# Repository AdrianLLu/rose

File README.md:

# Rose a MIT OpenAg Personal Food Computer (PFC) community-member-created project
Project URL: https://github.com/AdrianLLu/rose <br>
By Adrian L. Lu <br>
TODO Rose helps you ... <br>
MIT OpenAg Personal Food Computer (PFC) community-member-generated files <br>
For my build diary see: http://adrianllu.com/category/food-computer/ <br>
TODO: You are free to copy, modify, and distribute Rose with attribution under the terms of the <license>. See the LICENSE file for details.

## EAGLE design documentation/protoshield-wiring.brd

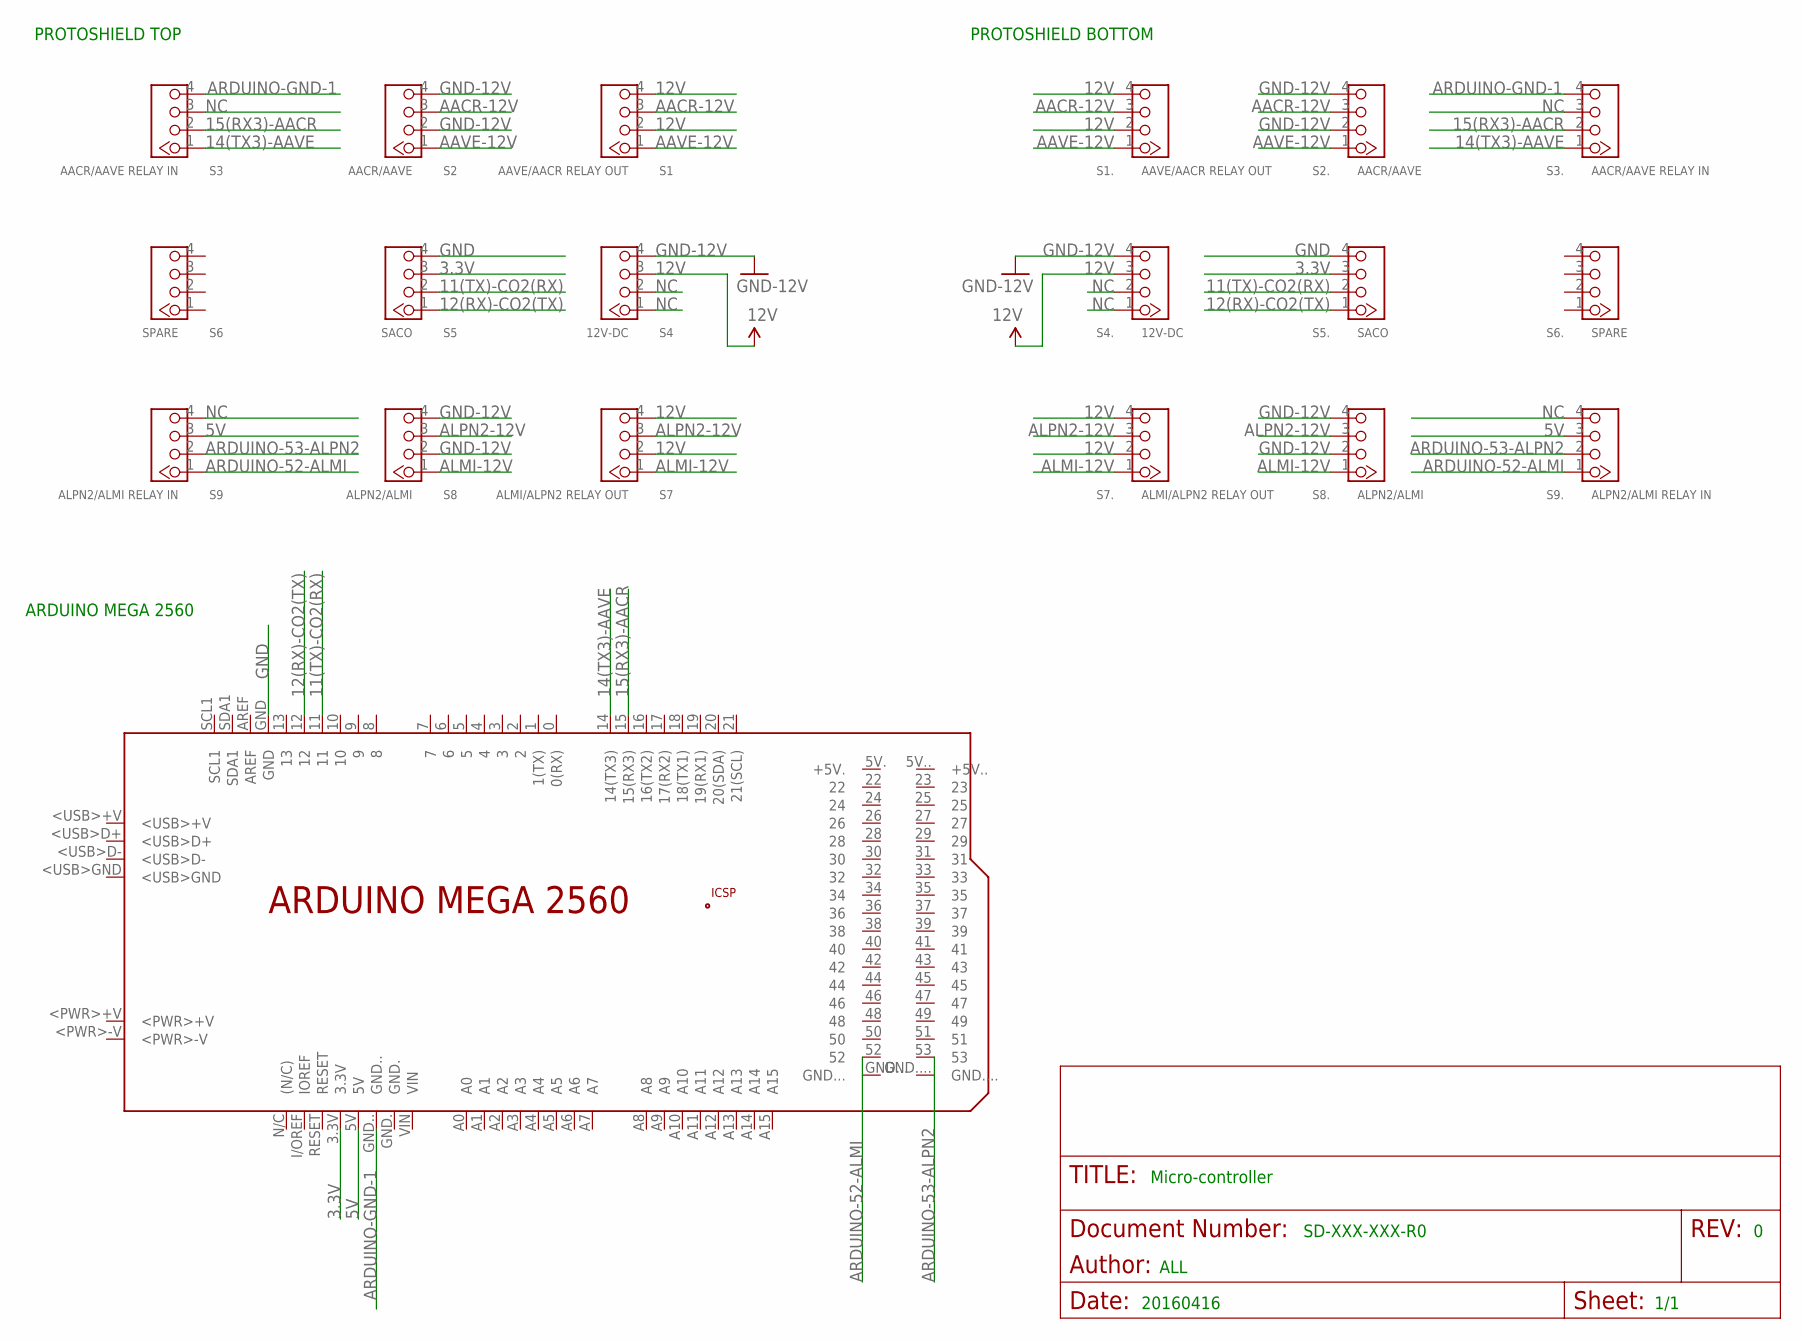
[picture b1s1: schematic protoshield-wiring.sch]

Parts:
PCB1: ARDUINO_MEGA2560
S1, S1.: AAVE/AACR RELAY OUT; HW4-2.0
S2, S2.: AACR/AAVE; HW4-2.0
S3, S3.: AACR/AAVE RELAY IN; HW4-2.0
S4, S4.: 12V-DC; HW4-2.0
S5, S5.: SACO; HW4-2.0
S6, S6.: SPARE; HW4-2.0
S7, S7.: ALMI/ALPN2 RELAY OUT; HW4-2.0
S8, S8.: ALPN2/ALMI; HW4-2.0
S9, S9.: ALPN2/ALMI RELAY IN; HW4-2.0

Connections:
3.3V: PCB1.3.3V, S5.3, S5..3
5V: PCB1.5V, S9.3, S9..3
11(TX)-CO2(RX): PCB1.11, S5.2, S5..2
12(RX)-CO2(TX): PCB1.12, S5.1, S5..1
12V: S1.2, S1.4, S1..2, S1..4, S4.3, S4..3, S7.2, S7.4, S7..2, S7..4
14(TX3)-AAVE: PCB1.14 (14(TX3)), S3.1, S3..1
15(RX3)-AACR: PCB1.15 (15(RX3)), S3.2, S3..2
AACR-12V: S1.3, S1..3, S2.3, S2..3
AAVE-12V: S1.1, S1..1, S2.1, S2..1
ALMI-12V: S7.1, S7..1, S8.1, S8..1
ALPN2-12V: S7.3, S7..3, S8.3, S8..3
ARDUINO-52-ALMI: S9.1, S9..1
ARDUINO-53-ALPN2: S9.2, S9..2
ARDUINO-GND-1: PCB1.GND.., S3.4, S3..4
GND: PCB1.GND, S5.4, S5..4
GND-12V: S2.2, S2.4, S2..2, S2..4, S4.4, S4..4, S8.2, S8.4, S8..2, S8..4
NC: S3.3, S3..3, S4.1, S4.2, S4..1, S4..2, S9.4, S9..4

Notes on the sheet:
Micro-controller
1/1
20160416
SD-XXX-XXX-R0
ALL
PROTOSHIELD TOP
ARDUINO MEGA 2560
PROTOSHIELD BOTTOM

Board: 2 copper layers, 19 parts (0 on the bottom side), 17 nets, no tracks yet.

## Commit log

2016-04-23 Added files via upload
    Protoshield wiring schematic
    For details on this part of the build see: http://adrianllu.com/2016/04/17/motherboard-build-notes-part-1-micro-controller-protoshield/
2016-04-23 Rename protoshield-wiring.brd to documentation/protoshield-wiring.brd
2016-04-23 Rename protoshield-wiring.sch to documentation/protoshield-wiring.sch
2016-04-23 Delete protoshield-wiring.pdf
    moved to documentation folder
2016-04-23 Added files via upload
    add .pdf file
2016-04-23 Added files via upload
2016-06-27 Add files via upload
    Added Creative Commons Attribution-ShareAlike 4.0 International License to documentation
2016-06-27 Update README.md
    minor revisions to README

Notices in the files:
parts and their libraries:
SparkFun-Aesthetics: Licensing: Creative Commons ShareAlike 4.0 International - https://creativecommons.org/licenses/by-sa/4.0
